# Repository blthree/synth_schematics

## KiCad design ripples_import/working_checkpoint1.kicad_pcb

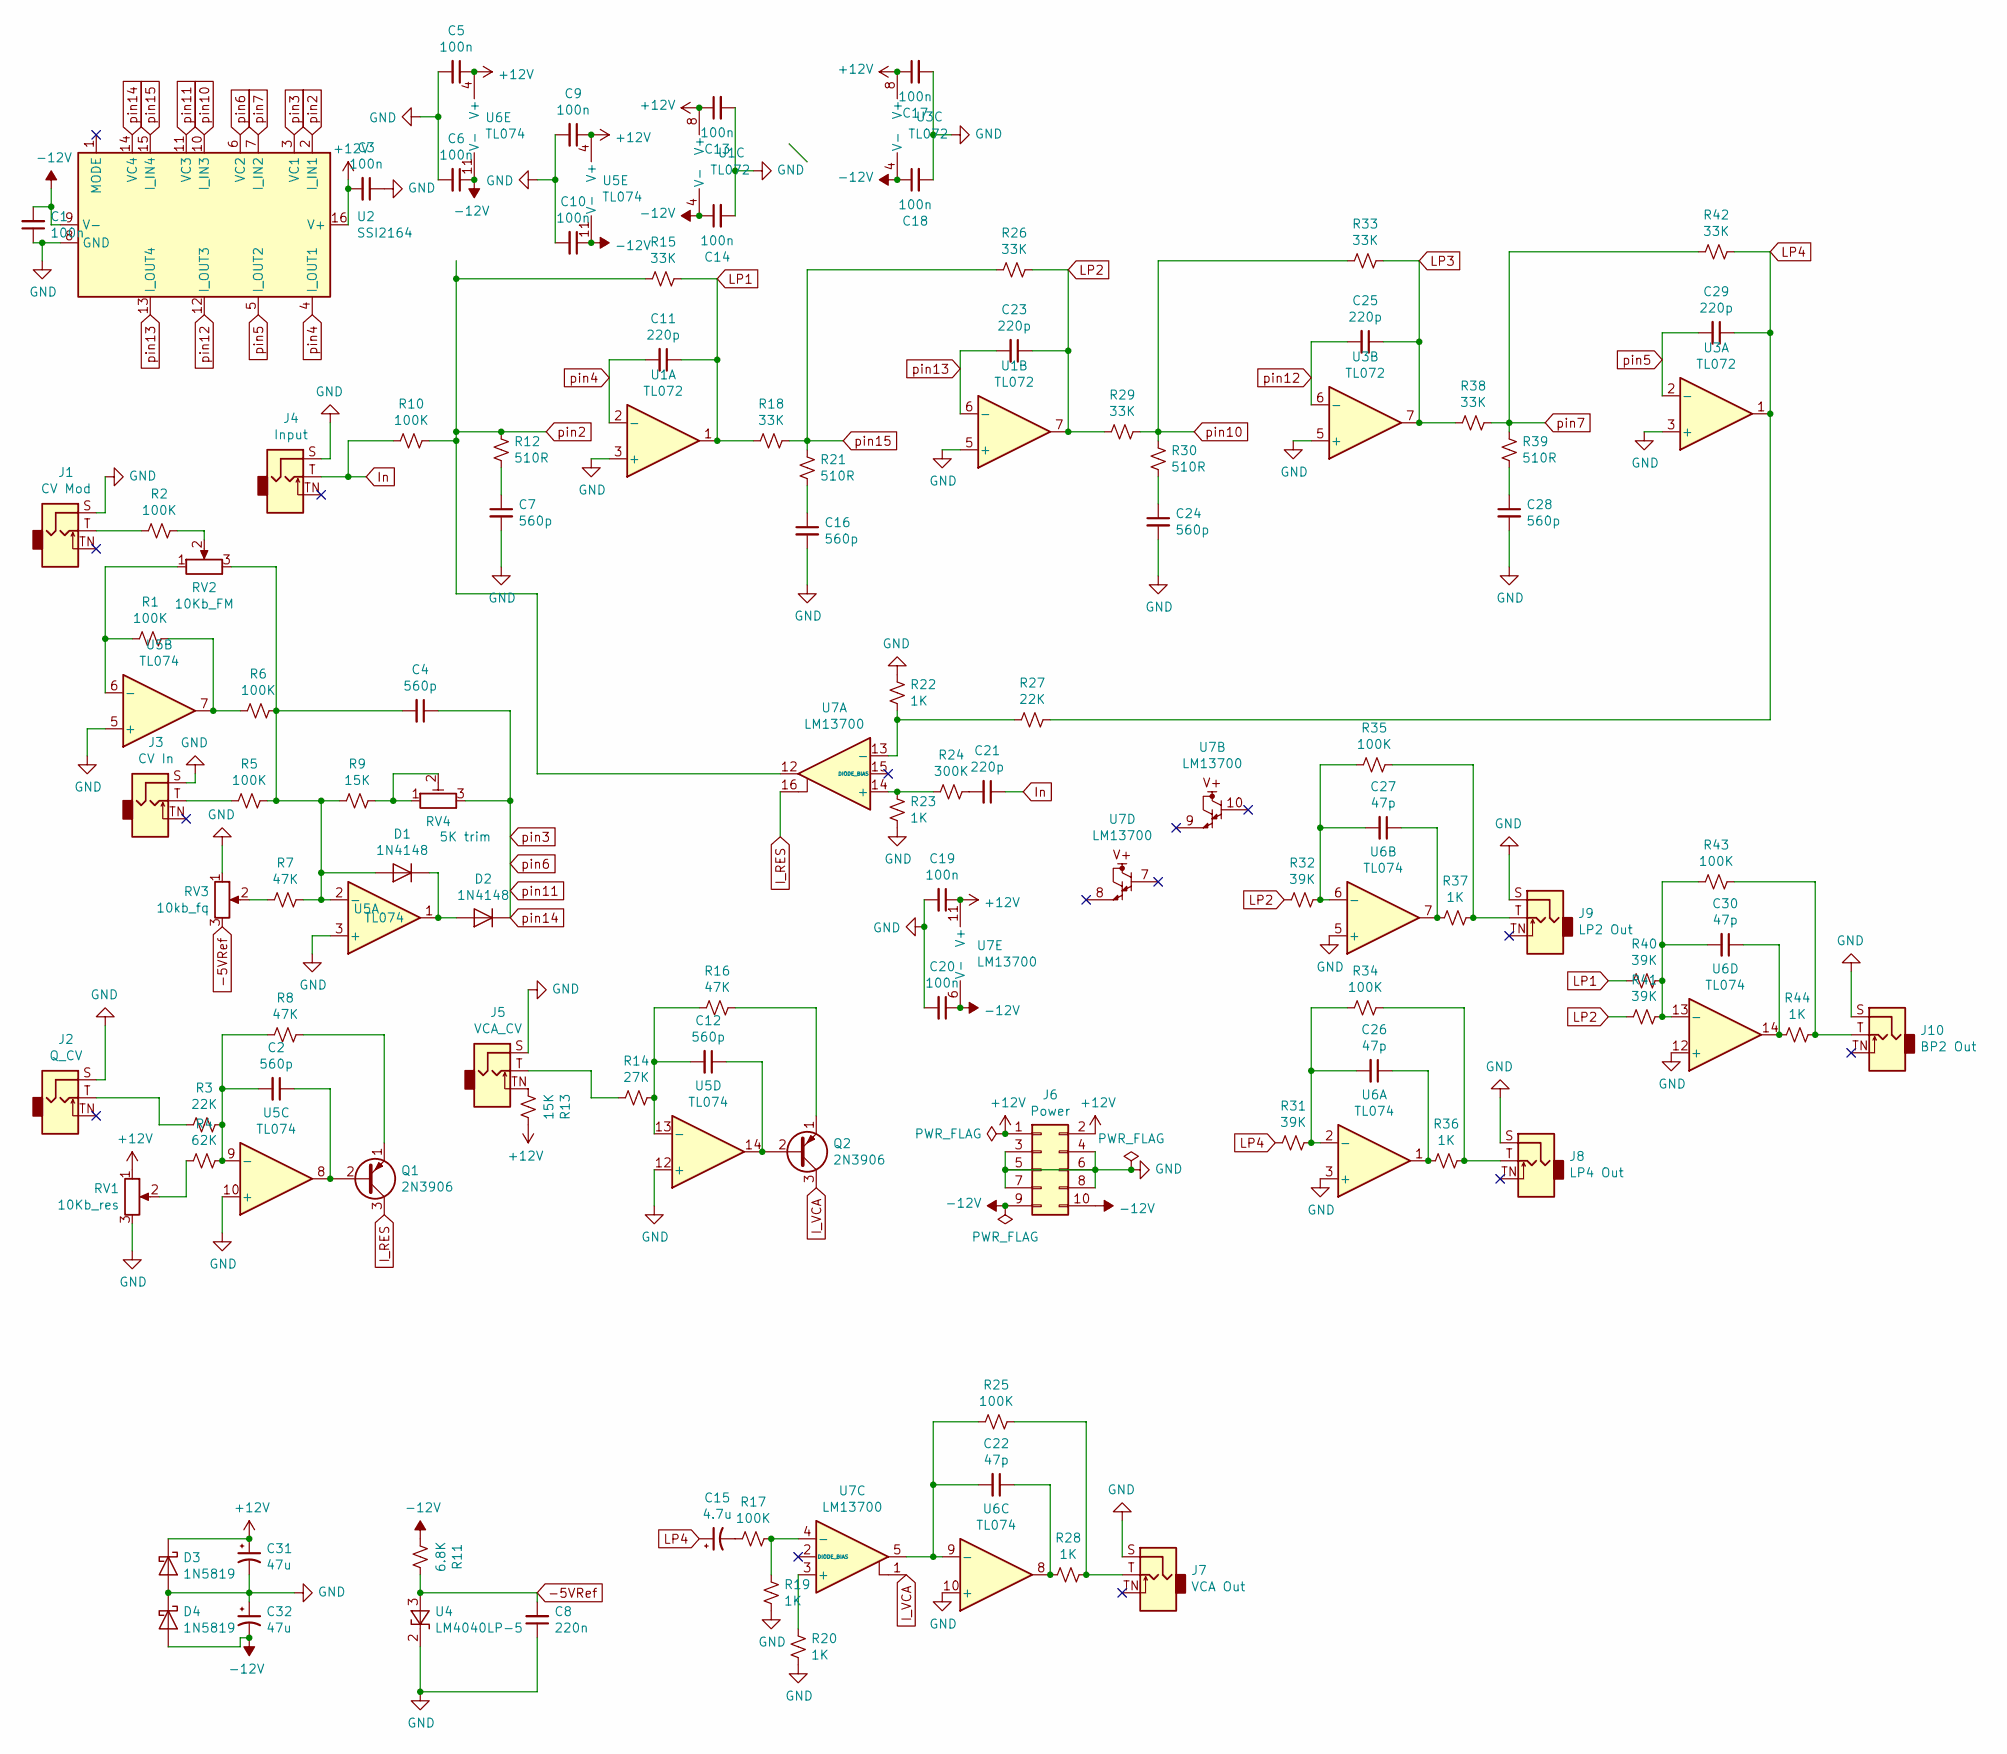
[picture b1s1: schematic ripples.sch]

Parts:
C1, C3, C5, C6, C9, C10, C13, C14, C17, C18, C19, C20: 100n; C_Disc_D5.1mm_W3.2mm_P5.00mm
C2, C4, C7, C12, C16, C24, C28: 560p; C_Disc_D5.1mm_W3.2mm_P5.00mm
C8: 220n; C_Disc_D5.1mm_W3.2mm_P5.00mm
C11, C21, C23, C25, C29: 220p; C_Disc_D5.1mm_W3.2mm_P5.00mm
C15: 4.7u; CP_Radial_D5.0mm_P2.00mm
C22, C26, C27, C30: 47p; C_Disc_D5.1mm_W3.2mm_P5.00mm
C31, C32: 47u; CP_Radial_D5.0mm_P2.00mm
D1, D2: 1N4148; D_DO-35_SOD27_P7.62mm_Horizontal
D3, D4: 1N5819; D_DO-41_SOD81_P10.16mm_Horizontal
J1: CV Mod; Jack_3.5mm_QingPu_WQP-PJ398SM_Vertical_CircularHoles
J2: Q_CV; Jack_3.5mm_QingPu_WQP-PJ398SM_Vertical_CircularHoles
J3: CV In; Jack_3.5mm_QingPu_WQP-PJ398SM_Vertical_CircularHoles
J4: Input; Jack_3.5mm_QingPu_WQP-PJ398SM_Vertical_CircularHoles
J5: VCA_CV; Jack_3.5mm_QingPu_WQP-PJ398SM_Vertical_CircularHoles
J6: Power; PinHeader_2x05_P2.54mm_Vertical
J7: VCA Out; Jack_3.5mm_QingPu_WQP-PJ398SM_Vertical_CircularHoles
J8: LP4 Out; Jack_3.5mm_QingPu_WQP-PJ398SM_Vertical_CircularHoles
J9: LP2 Out; Jack_3.5mm_QingPu_WQP-PJ398SM_Vertical_CircularHoles
J10: BP2 Out; Jack_3.5mm_QingPu_WQP-PJ398SM_Vertical_CircularHoles
Q1, Q2: 2N3906; TO-92_Inline
R1, R2, R5, R6, R10, R17, R25, R34, R35, R43: 100K; R_Axial_DIN0207_L6.3mm_D2.5mm_P5.08mm_Vertical
R3, R27: 22K; R_Axial_DIN0207_L6.3mm_D2.5mm_P5.08mm_Vertical
R4: 62K; R_Axial_DIN0207_L6.3mm_D2.5mm_P5.08mm_Vertical
R7, R8, R16: 47K; R_Axial_DIN0207_L6.3mm_D2.5mm_P5.08mm_Vertical
R9, R13: 15K; R_Axial_DIN0207_L6.3mm_D2.5mm_P5.08mm_Vertical
R11: 6.8K; R_Axial_DIN0207_L6.3mm_D2.5mm_P5.08mm_Vertical
R12, R21, R30, R39: 510R; R_Axial_DIN0207_L6.3mm_D2.5mm_P5.08mm_Vertical
R14: 27K; R_Axial_DIN0207_L6.3mm_D2.5mm_P5.08mm_Vertical
R15, R18, R26, R29, R33, R38, R42: 33K; R_Axial_DIN0207_L6.3mm_D2.5mm_P5.08mm_Vertical
R19, R20, R22, R23, R28, R36, R37, R44: 1K; R_Axial_DIN0207_L6.3mm_D2.5mm_P5.08mm_Vertical
R24: 300K; R_Axial_DIN0207_L6.3mm_D2.5mm_P5.08mm_Vertical
R31, R32, R40, R41: 39K; R_Axial_DIN0207_L6.3mm_D2.5mm_P5.08mm_Vertical
RV1: 10Kb_res; Potentiometer_Bourns_PTV09A-1_Single_Vertical
RV2: 10Kb_FM; Potentiometer_Bourns_PTV09A-1_Single_Vertical
RV3: 10kb_fq; Potentiometer_Bourns_PTV09A-1_Single_Vertical
RV4: 5K trim; Potentiometer_Bourns_3296X_Horizontal
U1, U3: TL072; DIP-8_W7.62mm_Socket
U2: SSI2164; DIP-16_W7.62mm_Socket
U4: LM4040LP-5; TO-92_Inline
U5, U6: TL074; DIP-14_W7.62mm_Socket
U7: LM13700; DIP-16_W7.62mm_Socket

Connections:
+12V: C3.2, C5.1, C9.1, C13.1, C17.1, C19.1, C31.1, D3.1 (K), J6.1, J6.2, R13.1, RV1.1, U1.8 (V+), U2.16 (V+), U3.8 (V+), U5.4 (V+), U6.4 (V+), U7.11 (V+)
-5VRef: C8.2, R11.1, RV3.3, U4.3 (A)
-12V: C1.2, C6.1, C10.1, C14.1, C18.1, C20.1, C32.2, D4.2 (A), J6.9, J6.10, R11.2, U1.4 (V-), U2.9 (V-), U3.4 (V-), U5.11 (V-), U6.11 (V-), U7.6 (V-)
GND: C1.1, C3.1, C5.2, C6.2, C7.2, C8.1, C9.2, C10.2, C13.2, C14.2, C16.2, C17.2, C18.2, C19.2, C20.2, C24.2, C28.2, C31.2, C32.1, D3.2 (A), D4.1 (K), J1.S, J2.S, J3.S, J4.S, J5.S, J6.3, J6.4, J6.5, J6.6, J6.7, J6.8, J7.S, J8.S, J9.S, J10.S, R19.1, R20.1, R22.2, R23.1, RV1.3, RV3.1, U1.3 (+), U1.5 (+), U2.8 (GND), U3.3 (+), U3.5 (+), U4.2 (K), U5.3 (+), U5.5 (+), U5.10 (+), U5.12 (+), U6.3 (+), U6.5 (+), U6.10 (+), U6.12 (+)
I_RES: Q1.3 (C), U7.16
I_VCA: Q2.3 (C), U7.1
In: C21.1, J4.T, R10.2
LP1: C11.1, R15.2, R18.1, R40.2, U1.1
LP2: C23.1, R26.2, R29.1, R32.2, R41.2, U1.7
LP3: C25.1, R33.2, R38.1, U3.7
LP4: C15.1, C29.1, R27.2, R31.2, R42.2, U3.1
unnamed: C2.1, Q1.2 (B), U5.8
unnamed: C2.2, R3.1, R4.1, R8.2, U5.9 (-)
unnamed: C4.2, D1.2 (A), R5.1, R6.1, R7.1, R9.2, RV2.3, U5.2 (-)
unnamed: C7.1, R12.1
unnamed: C12.1, Q2.2 (B), U5.14
unnamed: C12.2, R14.1, R16.2, U5.13 (-)
unnamed: C15.2, R17.2
unnamed: C16.1, R21.1
unnamed: C21.2, R24.2
unnamed: C22.1, R28.1, U6.8
unnamed: C22.2, R25.2, U6.9 (-), U7.5
unnamed: C24.1, R30.1
unnamed: C26.1, R36.1, U6.1
unnamed: C26.2, R31.1, R34.2, U6.2 (-)
unnamed: C27.1, R37.1, U6.7
unnamed: C27.2, R32.1, R35.2, U6.6 (-)
unnamed: C28.1, R39.1
unnamed: C30.1, R44.1, U6.14
unnamed: C30.2, R40.1, R41.1, R43.2, U6.13 (-)
unnamed: D1.1 (K), D2.2 (A), U5.1
unnamed: J1.T, R2.2
unnamed: J2.T, R3.2
unnamed: J3.T, R5.2
unnamed: J5.T, R14.2
unnamed: J5.TN, R13.2
unnamed: J7.T, R25.1, R28.2
unnamed: J8.T, R34.1, R36.2
unnamed: J9.T, R35.1, R37.2
unnamed: J10.T, R43.1, R44.2
unnamed: Q1.1 (E), R8.1
unnamed: Q2.1 (E), R16.1
unnamed: R1.1, R6.2, U5.7
unnamed: R1.2, RV2.1, U5.6 (-)
unnamed: R2.1, RV2.2
unnamed: R4.2, RV1.2
unnamed: R7.2, RV3.2
unnamed: R9.1, RV4.1, RV4.2
unnamed: R17.1, R19.2, U7.4 (-)
unnamed: R20.2, U7.3 (+)
unnamed: R22.1, R27.1, U7.13 (-)
unnamed: R23.2, R24.1, U7.14 (+)
pin2: R10.1, R12.2, R15.1, U2.2 (I_IN1), U7.12
pin4: C11.2, U1.2 (-), U2.4 (I_OUT1)
pin5: C29.2, U2.5 (I_OUT2), U3.2 (-)
pin7: R38.2, R39.2, R42.1, U2.7 (I_IN2)
pin10: R29.2, R30.2, R33.1, U2.10 (I_IN3)
pin11: C4.1, D2.1 (K), RV4.3, U2.3 (VC1), U2.6 (VC2), U2.11 (VC3), U2.14 (VC4)
pin12: C25.2, U2.12 (I_OUT3), U3.6 (-)
pin13: C23.2, U1.6 (-), U2.13 (I_OUT4)
pin15: R18.2, R21.2, R26.1, U2.15 (I_IN4)

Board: 2 copper layers, 103 parts (0 on the bottom side), 61 nets, no tracks yet.

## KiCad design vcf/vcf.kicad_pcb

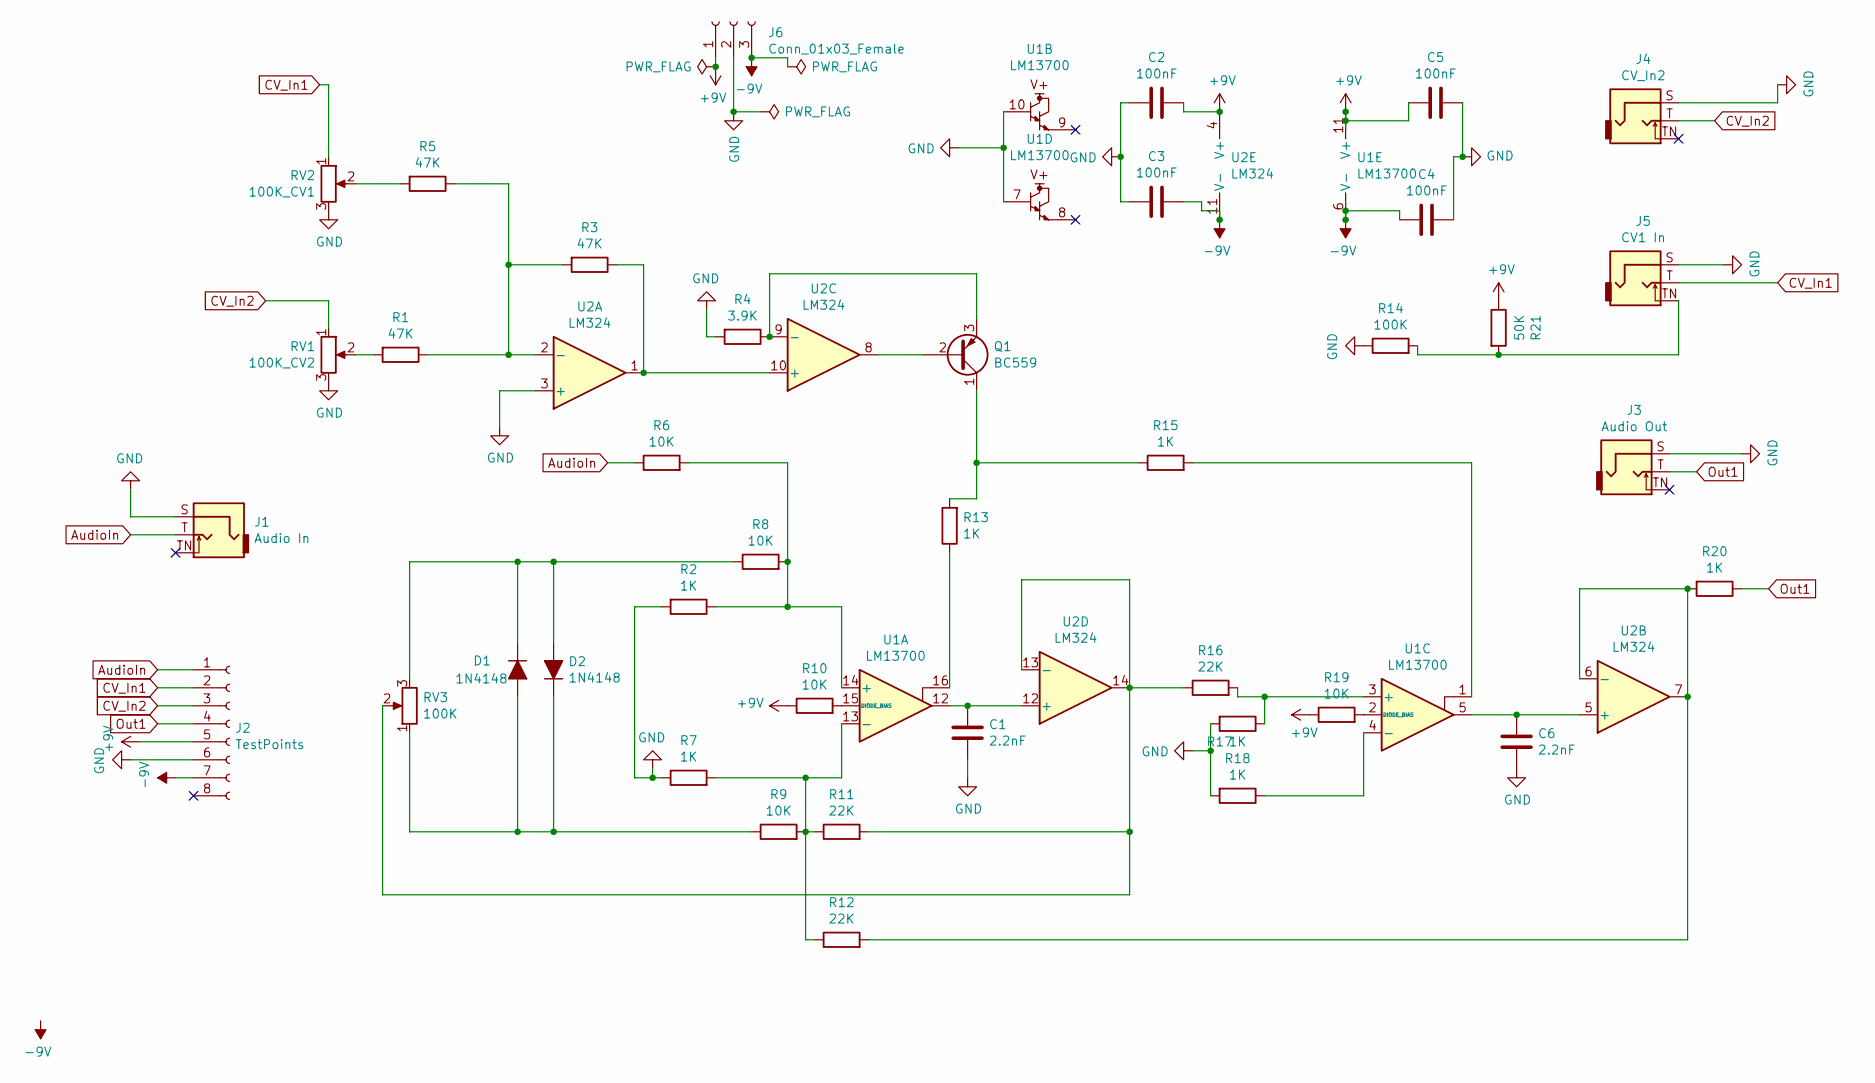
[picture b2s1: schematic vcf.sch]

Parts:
C1, C6: 2.2nF; C_Disc_D5.0mm_W2.5mm_P5.00mm
C2, C3, C4, C5: 100nF; C_Disc_D5.0mm_W2.5mm_P5.00mm
D1, D2: 1N4148; D_DO-35_SOD27_P7.62mm_Horizontal
J1: Audio In; CUI_SJ2-3592B-SMT-TR
J2: TestPoints; PinHeader_1x08_P2.54mm_Vertical
J3: Audio Out; CUI_SJ2-3592B-SMT-TR
J4: CV_In2; CUI_SJ2-3592B-SMT-TR
J5: CV1 In; CUI_SJ2-3592B-SMT-TR
J6: Conn_01x03_Female; JST_PH_B3B-PH-K_1x03_P2.00mm_Vertical
Q1: BC559; TO-92_Inline
R1, R3, R5: 47K; R_Axial_DIN0207_L6.3mm_D2.5mm_P5.08mm_Vertical
R2, R7, R13, R15, R17, R18, R20: 1K; R_Axial_DIN0207_L6.3mm_D2.5mm_P5.08mm_Vertical
R4: 3.9K; R_Axial_DIN0207_L6.3mm_D2.5mm_P5.08mm_Vertical
R6, R8, R9, R10, R19: 10K; R_Axial_DIN0207_L6.3mm_D2.5mm_P5.08mm_Vertical
R11, R12, R16: 22K; R_Axial_DIN0207_L6.3mm_D2.5mm_P5.08mm_Vertical
R14: 100K; R_Axial_DIN0207_L6.3mm_D2.5mm_P5.08mm_Vertical
R21: 50K; R_Axial_DIN0207_L6.3mm_D2.5mm_P5.08mm_Vertical
RV1: 100K_CV2; JST_PH_B3B-PH-K_1x03_P2.00mm_Vertical
RV2: 100K_CV1; JST_PH_B3B-PH-K_1x03_P2.00mm_Vertical
RV3: 100K; JST_PH_B3B-PH-K_1x03_P2.00mm_Vertical
U1: LM13700; DIP-16_W7.62mm_Socket
U2: LM324; DIP-14_W7.62mm_Socket

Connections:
+9V: C2.1, C5.2, J2.5, J6.1, R10.1, R19.1, R21.1, U1.11 (V+), U2.4 (V+)
-9V: C3.1, C4.2, J2.7, J6.3, U1.6 (V-), U2.11 (V-)
AudioIn: J1.T, J2.1, R6.1
CV_In1: J2.2, J5.T, RV2.1
CV_In2: J2.3, J4.T, RV1.1
GND: C1.2, C2.2, C3.2, C4.1, C5.1, C6.2, J1.S, J2.6, J3.S, J4.S, J5.S, J6.2, R2.2, R4.2, R7.1, R14.1, R17.2, R18.2, RV1.3, RV2.3, U1.7, U1.10, U2.3 (+)
unnamed: C1.1, U1.12, U2.12 (+)
unnamed: C6.1, U1.5, U2.5 (+)
unnamed: D1.1 (K), D2.2 (A), R8.1, RV3.3
unnamed: D1.2 (A), D2.1 (K), R9.1, RV3.1
unnamed: J5.TN, R14.2, R21.2
unnamed: Q1.1 (C), R13.2, R15.1
unnamed: Q1.2 (B), U2.8
unnamed: Q1.3 (E), R4.1, U2.9 (-)
unnamed: R1.1, R3.2, R5.1, U2.2 (-)
unnamed: R1.2, RV1.2
unnamed: R2.1, R6.2, R8.2, U1.14 (+)
unnamed: R3.1, U2.1, U2.10 (+)
unnamed: R5.2, RV2.2
unnamed: R10.2, U1.15 (DIODE_BIAS)
unnamed: R7.2, R9.2, R11.1, R12.1, U1.13 (-)
unnamed: R11.2, R16.1, RV3.2, U2.13 (-), U2.14
unnamed: R12.2, R20.2, U2.6 (-), U2.7
unnamed: R13.1, U1.16
unnamed: R15.2, U1.1
unnamed: R16.2, R17.1, U1.3 (+)
unnamed: R18.1, U1.4 (-)
unnamed: R19.2, U1.2 (DIODE_BIAS)
Out1: J2.4, J3.T, R20.1

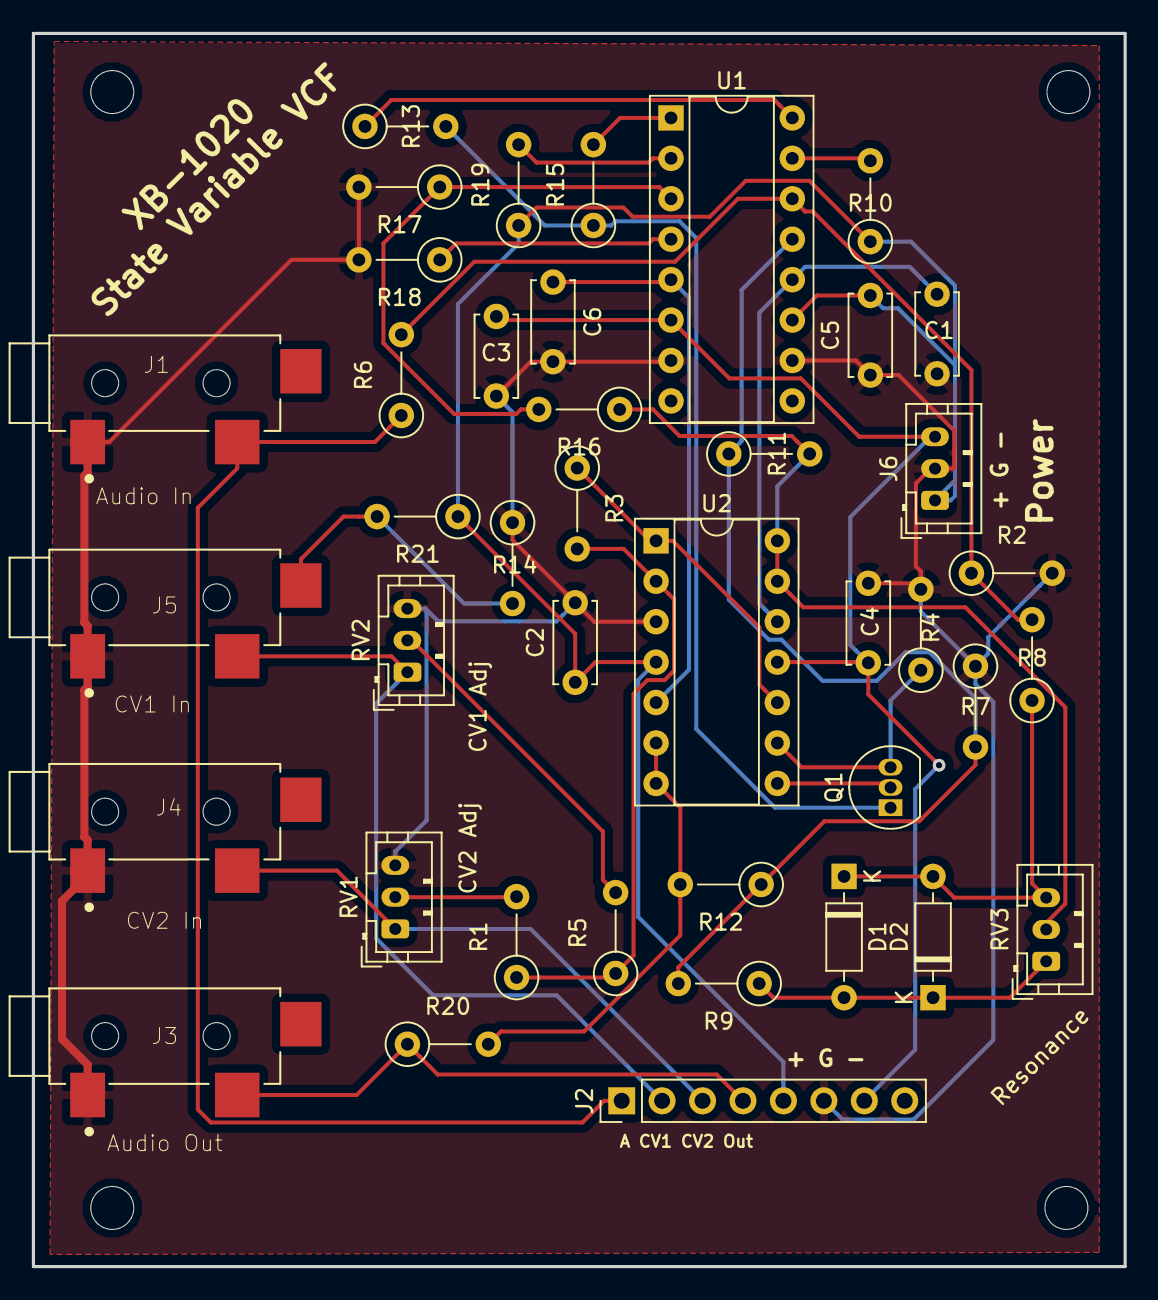
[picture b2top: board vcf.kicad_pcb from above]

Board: 2 copper layers, 68.6 x 77.5 mm, 41 parts (0 on the bottom side), 29 nets.

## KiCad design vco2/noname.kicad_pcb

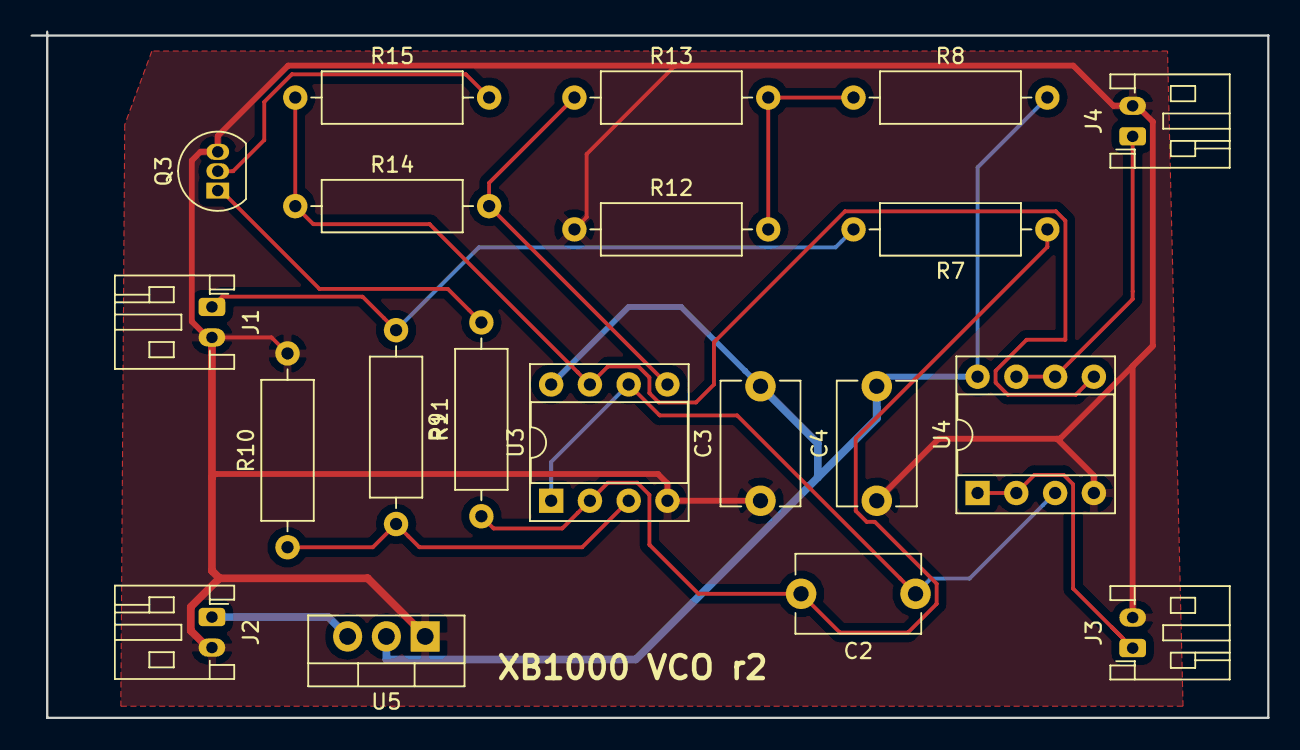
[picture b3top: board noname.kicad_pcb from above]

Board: 2 copper layers, 81.0 x 45.0 mm, 20 parts (0 on the bottom side), 14 nets.

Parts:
C2: 4.7nf; C_Disc_D8.0mm_W5.0mm_P7.50mm
C3, C4: 100nF; C_Disc_D8.0mm_W5.0mm_P7.50mm
J1: Input; JST_PH_S2B-PH-K_1x02_P2.00mm_Horizontal
J2: Power In; JST_PH_S2B-PH-K_1x02_P2.00mm_Horizontal
J3: Triangle Out; JST_PH_S2B-PH-K_1x02_P2.00mm_Horizontal
J4: Square Out; JST_PH_S2B-PH-K_1x02_P2.00mm_Horizontal
Q3: BC548; TO-92_Inline
R7, R8, R12, R14, R15: 100K; R_Axial_DIN0309_L9.0mm_D3.2mm_P12.70mm_Horizontal
R9, R10, R11, R13: 56K; R_Axial_DIN0309_L9.0mm_D3.2mm_P12.70mm_Horizontal
U3, U4: LM358; DIP-8_W7.62mm_Socket
U5: +5V Linear Regulator; TO-220-3_Vertical

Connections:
+5V: C3.2, C4.2, R8.2, U3.8, U4.8, U5.2
GND: C3.1, C4.1, J1.2, J2.2, J3.2, J4.2, Q3.3, R10.2, R12.1, U3.4, U4.4, U5.1
unnamed: C2.1, U3.1, U3.6, U4.3
unnamed: C2.2, R7.1, R11.1, U3.2
unnamed: J1.1, R7.2, R9.1
unnamed: J2.1, U5.3
unnamed: J3.1, U4.1, U4.2
unnamed: J4.1, U4.6, U4.7
unnamed: Q3.1, R11.2
unnamed: Q3.2, R15.2
unnamed: R9.2, R10.1, U3.3
unnamed: R8.1, R12.2, R13.2
unnamed: R13.1, R14.2, U3.5
unnamed: R14.1, R15.1, U3.7, U4.5

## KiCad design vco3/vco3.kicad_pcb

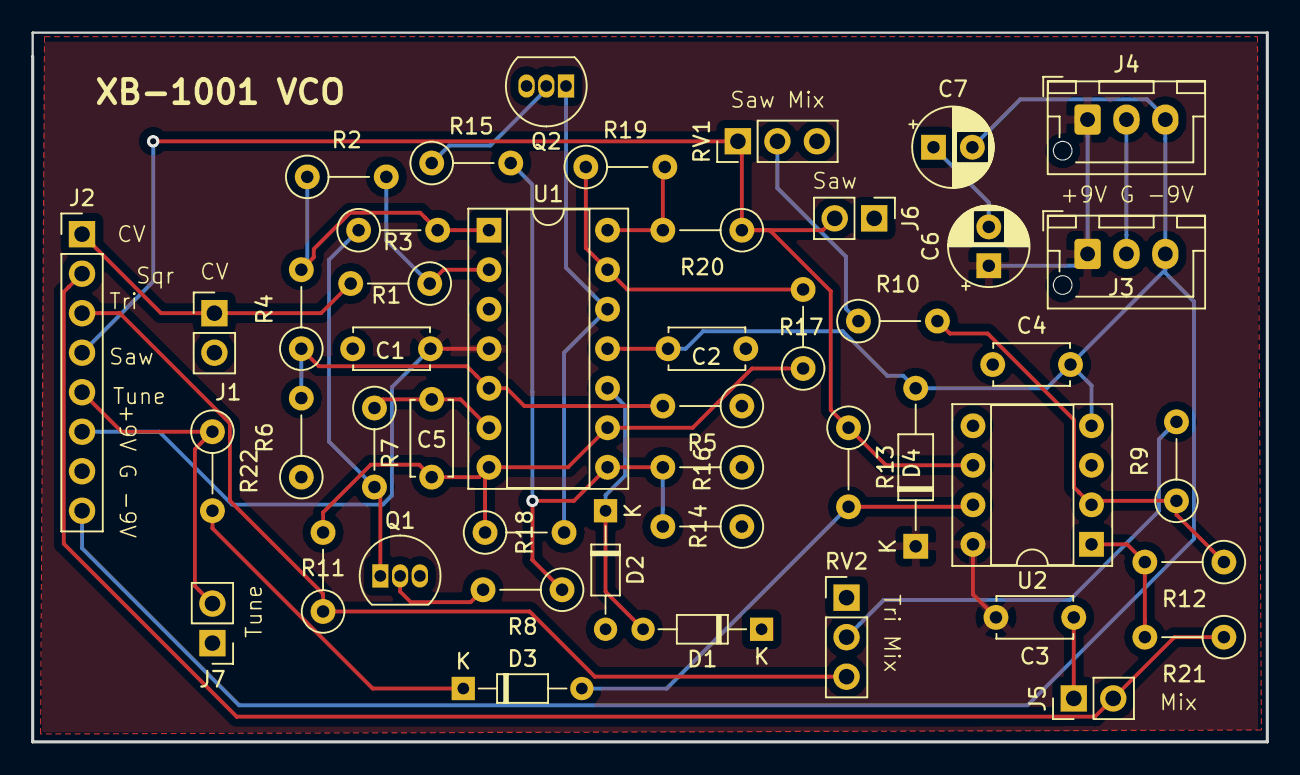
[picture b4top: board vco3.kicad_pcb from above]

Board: 2 copper layers, 79.4 x 45.6 mm, 46 parts (0 on the bottom side), 27 nets.

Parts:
C1, C2, C3, C4: 100nF; C_Disc_D4.7mm_W2.5mm_P5.00mm
C5: 47nF; C_Disc_D4.7mm_W2.5mm_P5.00mm
C6, C7: CP; CP_Radial_D5.0mm_P2.50mm
D1, D2, D3: 1N4148; D_DO-34_SOD68_P7.62mm_Horizontal
D4: 1N4001; D_DO-35_SOD27_P10.16mm_Horizontal
J1: CV Input; PinHeader_1x02_P2.54mm_Vertical
J2: Test Points; PinHeader_1x08_P2.54mm_Vertical
J3: Power A; JST_XH_B03B-XH-AM_1x03_P2.50mm_Vertical
J4: Power B; JST_XH_B03B-XH-AM_1x03_P2.50mm_Vertical
J5: Mix Out; PinHeader_1x02_P2.54mm_Vertical
J6: Saw Out; PinHeader_1x02_P2.54mm_Vertical
J7: Tune Out; PinHeader_1x02_P2.54mm_Vertical
Q1: BC559; TO-92_Inline
Q2: BC549; TO-92_Inline
R1, R2: 47K; R_Axial_DIN0207_L6.3mm_D2.5mm_P5.08mm_Vertical
R3, R7, R8, R15: 22K; R_Axial_DIN0207_L6.3mm_D2.5mm_P5.08mm_Vertical
R4, R5, R6, R13, R14, R17, R18, R19: 100K; R_Axial_DIN0207_L6.3mm_D2.5mm_P5.08mm_Vertical
R9, R10: 10K; R_Axial_DIN0207_L6.3mm_D2.5mm_P5.08mm_Vertical
R11, R16, R20, R21, R22: 1K; R_Axial_DIN0207_L6.3mm_D2.5mm_P5.08mm_Vertical
R12: 56K; R_Axial_DIN0207_L6.3mm_D2.5mm_P5.08mm_Vertical
RV1, RV2: 100K; PinHeader_1x03_P2.54mm_Vertical
U1: LM324; DIP-14_W7.62mm_Socket
U2: TL072; DIP-8_W7.62mm_Socket

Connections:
+9V: C1.2, C3.2, C6.1, D4.1, J2.6, J3.1, J4.1, U1.4, U2.8
-9V: C2.2, C4.2, C7.2, D4.2, J2.8, J3.3, J4.3, U1.11, U2.4
CV_In: J1.1, J2.1, R1.2
GND: C1.1, C2.1, C3.1, C4.1, C6.2, C7.1, D1.1, D2.2, J1.2, J2.7, J3.2, J4.2, J5.1, J6.1, J7.1, Q1.3, Q2.3, R5.1, R6.1, R14.1, U1.3, U2.3, U2.5
MixOut: J2.2, J5.2, R21.1
unnamed: C5.1, R11.2, R17.1, R18.1, U1.7, U1.9
unnamed: C5.2, R7.1, U1.6
unnamed: D1.2, D2.1, U1.10
unnamed: D3.1, R22.2
unnamed: D3.2, R13.2, U2.7
unnamed: Q1.1, R3.1, R7.2
unnamed: Q1.2, R8.2
unnamed: Q2.1, R18.2, U1.12
unnamed: Q2.2, R15.1
unnamed: R1.1, R2.2, U1.2
unnamed: R2.1, R3.2, R4.2, U1.1
unnamed: R4.1, R5.2, R6.2, U1.5
unnamed: R9.2, RV2.2
unnamed: R10.1, RV1.2
unnamed: R9.1, R10.2, R12.1, U2.2
unnamed: R12.2, R21.2, U2.1
unnamed: R8.1, R14.2, R15.2, R16.2, U1.8
unnamed: R17.2, R19.1, U1.13
unnamed: R19.2, R20.2, U1.14
SawOut: J2.4, J6.2, R13.1, R20.1, RV1.1, U2.6
SubTriOut: J2.3, R11.1, RV2.3
TuneOut: J2.5, J7.2, R22.1

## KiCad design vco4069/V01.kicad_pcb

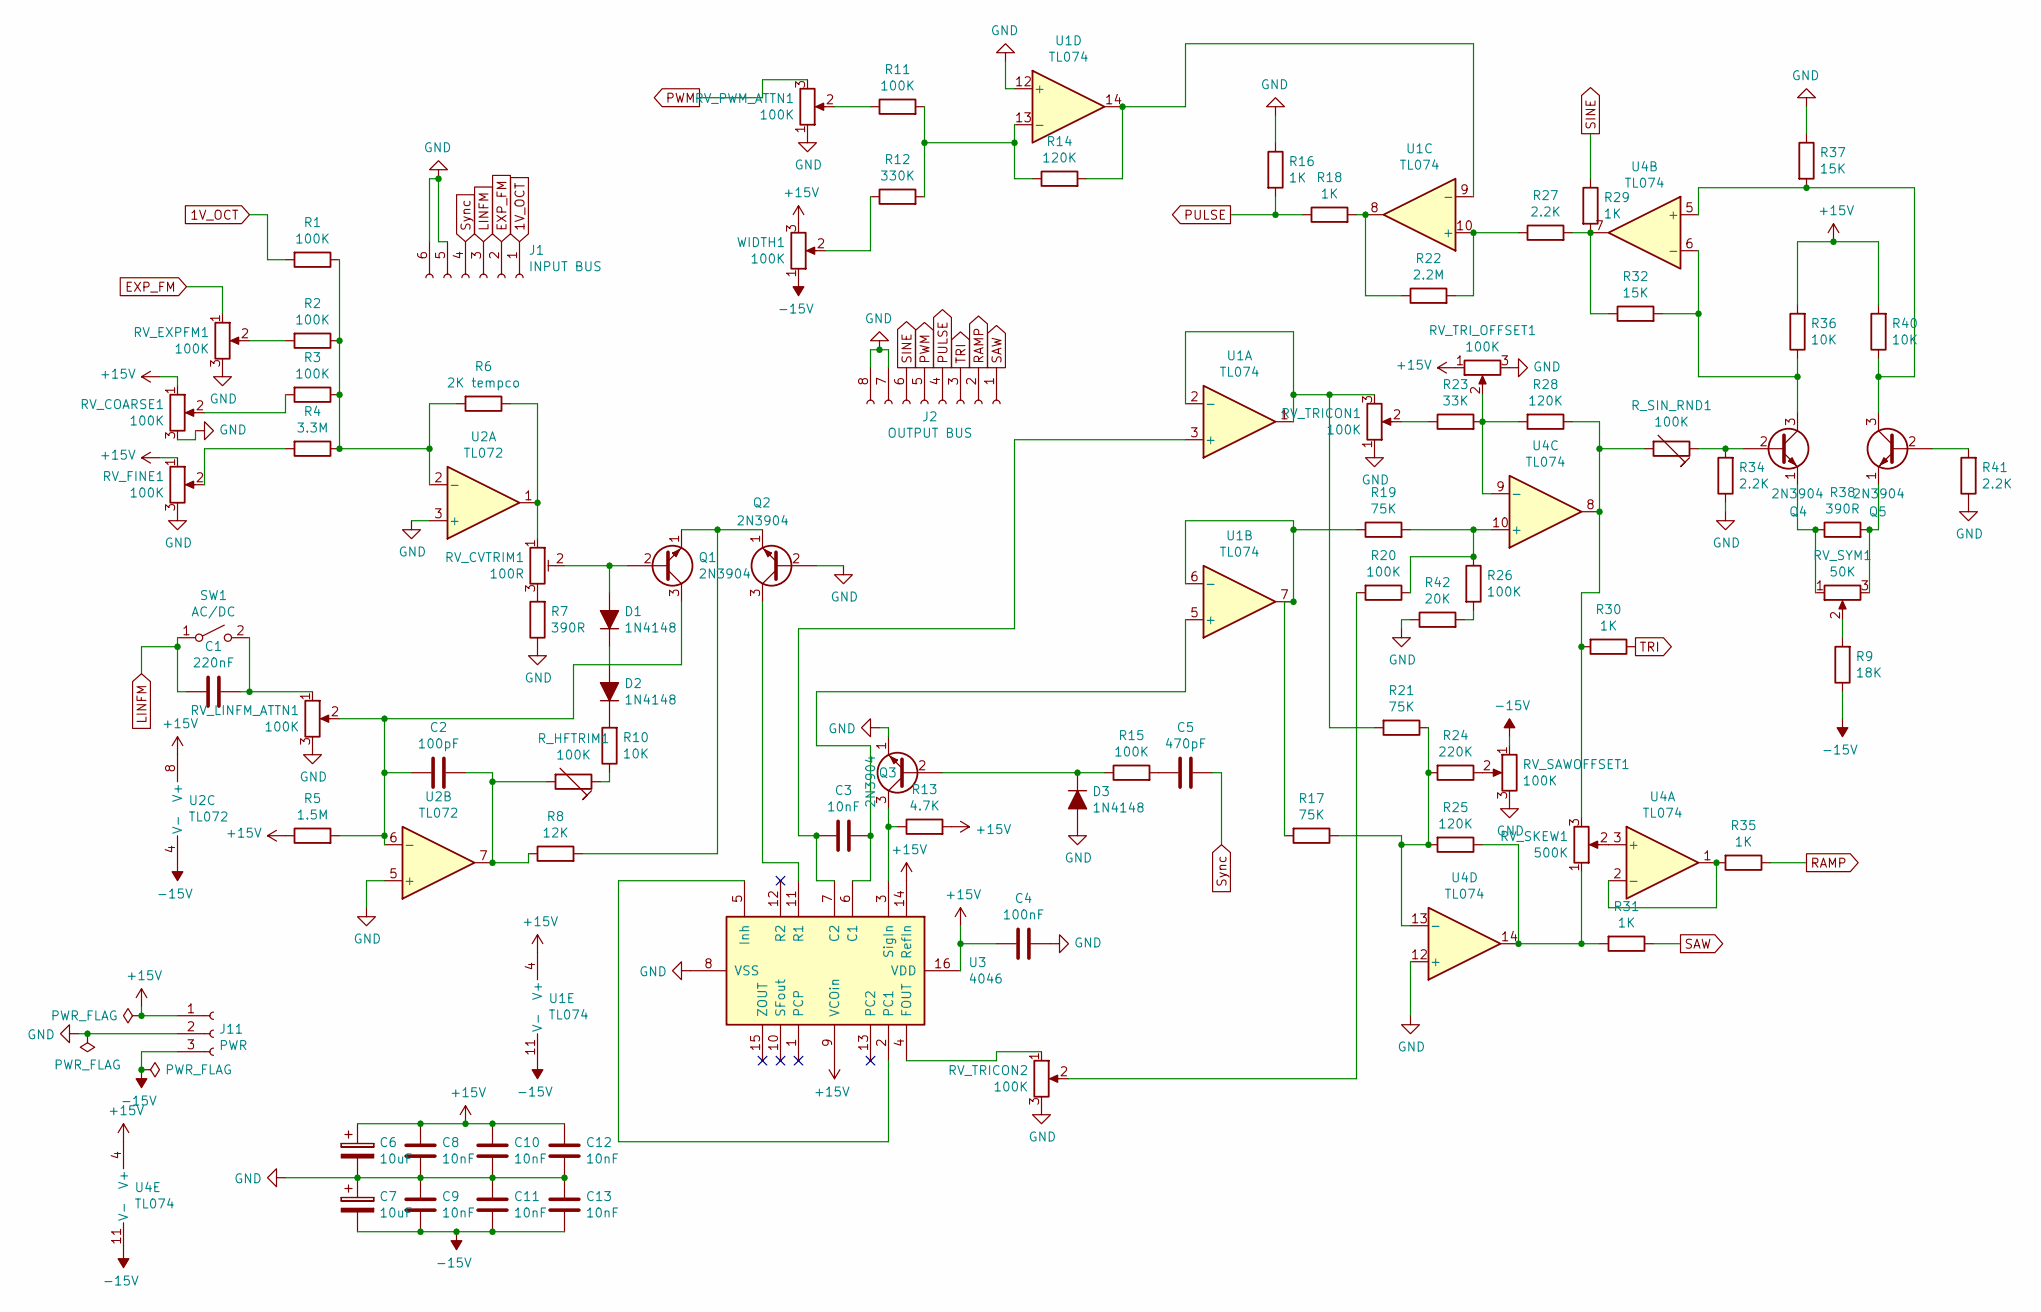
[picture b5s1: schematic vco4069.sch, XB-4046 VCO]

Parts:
C1: 220nF; C_Disc_D4.7mm_W2.5mm_P5.00mm
C2: 100pF; C_Disc_D4.7mm_W2.5mm_P5.00mm
C3, C8, C9, C10, C11, C12, C13: 10nF; C_Disc_D4.7mm_W2.5mm_P5.00mm
C4: 100nF; C_Disc_D4.7mm_W2.5mm_P5.00mm
C5: 470pF; C_Disc_D4.7mm_W2.5mm_P5.00mm
C6, C7: 10uF; CP_Radial_D10.0mm_P5.00mm
D1, D2, D3: 1N4148; D_DO-35_SOD27_P7.62mm_Horizontal
J1: INPUT BUS; PinHeader_1x06_P2.54mm_Vertical
J2: OUTPUT BUS; PinHeader_1x08_P2.54mm_Vertical
J11: PWR; PinHeader_1x03_P2.54mm_Vertical
Q1, Q2, Q3, Q4, Q5: 2N3904; TO-92_Inline
R1, R2, R3, R11, R15, R20, R26: 100K; R_Axial_DIN0207_L6.3mm_D2.5mm_P5.08mm_Vertical
R4: 3.3M; R_Axial_DIN0207_L6.3mm_D2.5mm_P5.08mm_Vertical
R5: 1.5M; R_Axial_DIN0207_L6.3mm_D2.5mm_P5.08mm_Vertical
R6: 2K tempco; R_Axial_DIN0207_L6.3mm_D2.5mm_P5.08mm_Vertical
R7, R38: 390R; R_Axial_DIN0207_L6.3mm_D2.5mm_P5.08mm_Vertical
R8: 12K; R_Axial_DIN0207_L6.3mm_D2.5mm_P5.08mm_Vertical
R9: 18K; R_Axial_DIN0207_L6.3mm_D2.5mm_P5.08mm_Vertical
R10, R36, R40: 10K; R_Axial_DIN0207_L6.3mm_D2.5mm_P5.08mm_Vertical
R12: 330K; R_Axial_DIN0207_L6.3mm_D2.5mm_P5.08mm_Vertical
R13: 4.7K; R_Axial_DIN0207_L6.3mm_D2.5mm_P5.08mm_Vertical
R14, R25, R28: 120K; R_Axial_DIN0207_L6.3mm_D2.5mm_P5.08mm_Vertical
R16, R18, R29, R30, R31, R35: 1K; R_Axial_DIN0207_L6.3mm_D2.5mm_P5.08mm_Vertical
R17, R19, R21: 75K; R_Axial_DIN0207_L6.3mm_D2.5mm_P5.08mm_Vertical
R22: 2.2M; R_Axial_DIN0207_L6.3mm_D2.5mm_P5.08mm_Vertical
R23: 33K; R_Axial_DIN0207_L6.3mm_D2.5mm_P5.08mm_Vertical
R24: 220K; R_Axial_DIN0207_L6.3mm_D2.5mm_P5.08mm_Vertical
R27, R34, R41: 2.2K; R_Axial_DIN0207_L6.3mm_D2.5mm_P5.08mm_Vertical
R32, R37: 15K; R_Axial_DIN0207_L6.3mm_D2.5mm_P5.08mm_Vertical
R42: 20K; R_Axial_DIN0207_L6.3mm_D2.5mm_P5.08mm_Vertical
RV_COARSE1: 100K; PinHeader_1x03_P2.54mm_Vertical
RV_CVTRIM1: 100R; Potentiometer_Bourns_3296Z_Horizontal
RV_EXPFM1: 100K; PinHeader_1x03_P2.54mm_Vertical
RV_FINE1: 100K; PinHeader_1x03_P2.54mm_Vertical
RV_LINFM_ATTN1: 100K; PinHeader_1x03_P2.54mm_Vertical
RV_PWM_ATTN1: 100K; PinHeader_1x03_P2.54mm_Vertical
RV_SAWOFFSET1: 100K; PinHeader_1x03_P2.54mm_Vertical
RV_SKEW1: 500K; PinHeader_1x03_P2.54mm_Vertical
RV_SYM1: 50K; Potentiometer_Bourns_3296W_Vertical
RV_TRICON1, RV_TRICON2: 100K; PinHeader_1x03_P2.54mm_Vertical
RV_TRI_OFFSET1: 100K; PinHeader_1x03_P2.54mm_Vertical
R_HFTRIM1: 100K; Potentiometer_Bourns_3296W_Vertical
R_SIN_RND1: 100K; Potentiometer_Bourns_3296W_Vertical
SW1: AC/DC; PinHeader_1x02_P2.54mm_Vertical
U1, U4: TL074; DIP-14_W7.62mm_Socket
U2: TL072; DIP-8_W7.62mm_Socket
U3: 4046; DIP-16_W7.62mm_Socket
WIDTH1: 100K; PinHeader_1x03_P2.54mm_Vertical

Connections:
1V_OCT: J1.1, R1.2
+15V: C4.2, C6.1, C8.2, C10.2, C12.2, J11.1, R5.1, R13.2, R36.2, R40.2, RV_COARSE1.1, RV_FINE1.1, RV_TRI_OFFSET1.1, U1.4 (V+), U2.8 (V+), U3.9 (VCOin), U3.14 (RefIn), U3.16 (VDD), U4.4 (V+), WIDTH1.3
-15V: C7.2, C9.1, C11.1, C13.1, J11.3, R9.1, RV_SAWOFFSET1.1, U1.11 (V-), U2.4 (V-), U4.11 (V-), WIDTH1.1
EXP_FM: J1.2, RV_EXPFM1.1
GND: C4.1, C6.2, C7.1, C8.1, C9.2, C10.1, C11.2, C12.1, C13.2, D3.2 (A), J1.5, J1.6, J2.7, J2.8, J11.2, Q2.2 (B), Q3.1 (E), R7.1, R16.1, R34.1, R37.1, R41.1, R42.1, RV_COARSE1.3, RV_EXPFM1.3, RV_FINE1.3, RV_LINFM_ATTN1.3, RV_PWM_ATTN1.1, RV_SAWOFFSET1.3, RV_TRICON1.1, RV_TRICON2.3, RV_TRI_OFFSET1.3, U1.12 (+), U2.3 (+), U2.5 (+), U3.8 (VSS), U4.12 (+)
LINFM: C1.2, J1.3, SW1.1 (A)
unnamed: C1.1, RV_LINFM_ATTN1.1, SW1.2 (B)
unnamed: C2.1, R8.1, R_HFTRIM1.2, U2.7
unnamed: C2.2, Q1.3 (C), R5.2, RV_LINFM_ATTN1.2, U2.6 (-)
unnamed: C3.1, U1.5 (+), U3.6 (C1)
unnamed: C3.2, U1.3 (+), U3.7 (C2)
unnamed: C5.2, R15.2
unnamed: D1.1 (K), D2.2 (A)
unnamed: D1.2 (A), Q1.2 (B), RV_CVTRIM1.2
unnamed: D2.1 (K), R10.2
unnamed: D3.1 (K), Q3.2 (B), R15.1
unnamed: Q1.1 (E), Q2.1 (E), R8.2
unnamed: Q2.3 (C), U3.11 (R1)
unnamed: Q3.3 (C), R13.1, U3.3 (SigIn)
unnamed: Q4.1 (E), R38.1, RV_SYM1.1
unnamed: Q4.2 (B), R34.2, R_SIN_RND1.1
unnamed: Q4.3 (C), R32.2, R36.1, U4.6 (-)
unnamed: Q5.1 (E), R38.2, RV_SYM1.3
unnamed: Q5.2 (B), R41.2
unnamed: Q5.3 (C), R37.2, R40.1, U4.5 (+)
unnamed: R1.1, R2.1, R3.1, R4.1, R6.2, U2.2 (-)
unnamed: R2.2, RV_EXPFM1.2
unnamed: R3.2, RV_COARSE1.2
unnamed: R4.2, RV_FINE1.2
unnamed: R6.1, RV_CVTRIM1.1, U2.1
unnamed: R7.2, RV_CVTRIM1.3
unnamed: R9.2, RV_SYM1.2
unnamed: R10.1, R_HFTRIM1.1
unnamed: R11.1, RV_PWM_ATTN1.2
unnamed: R11.2, R12.2, R14.1, U1.13 (-)
unnamed: R12.1, WIDTH1.2
unnamed: R14.2, U1.9 (-), U1.14
unnamed: R17.1, R21.1, R24.2, R25.2, U4.13 (-)
unnamed: R17.2, R19.1, U1.6 (-), U1.7
unnamed: R18.2, R22.1, U1.8
unnamed: R19.2, R20.1, R26.1, U4.10 (+)
unnamed: R20.2, RV_TRICON2.2
unnamed: R21.2, RV_TRICON1.3, U1.1, U1.2 (-)
unnamed: R22.2, R27.1, U1.10 (+)
unnamed: R23.1, RV_TRICON1.2
unnamed: R23.2, R28.2, RV_TRI_OFFSET1.2, U4.9 (-)
unnamed: R24.1, RV_SAWOFFSET1.2
unnamed: R25.1, R31.2, RV_SKEW1.1, U4.14
unnamed: R26.2, R42.2
unnamed: R27.2, R29.2, R32.1, U4.7
unnamed: R28.1, R30.2, RV_SKEW1.3, R_SIN_RND1.2, U4.8
unnamed: R35.2, U4.1, U4.2 (-)
unnamed: RV_SKEW1.2, U4.3 (+)
unnamed: RV_TRICON2.1, U3.4 (FOUT)
unnamed: U3.2 (PC1), U3.5 (Inh)
PULSE: J2.4, R16.2, R18.1
PWM: J2.5, RV_PWM_ATTN1.3
RAMP: J2.2, R35.1
SAW: J2.1, R31.1
SINE: J2.6, R29.1
Sync: C5.1, J1.4
TRI: J2.3, R30.1

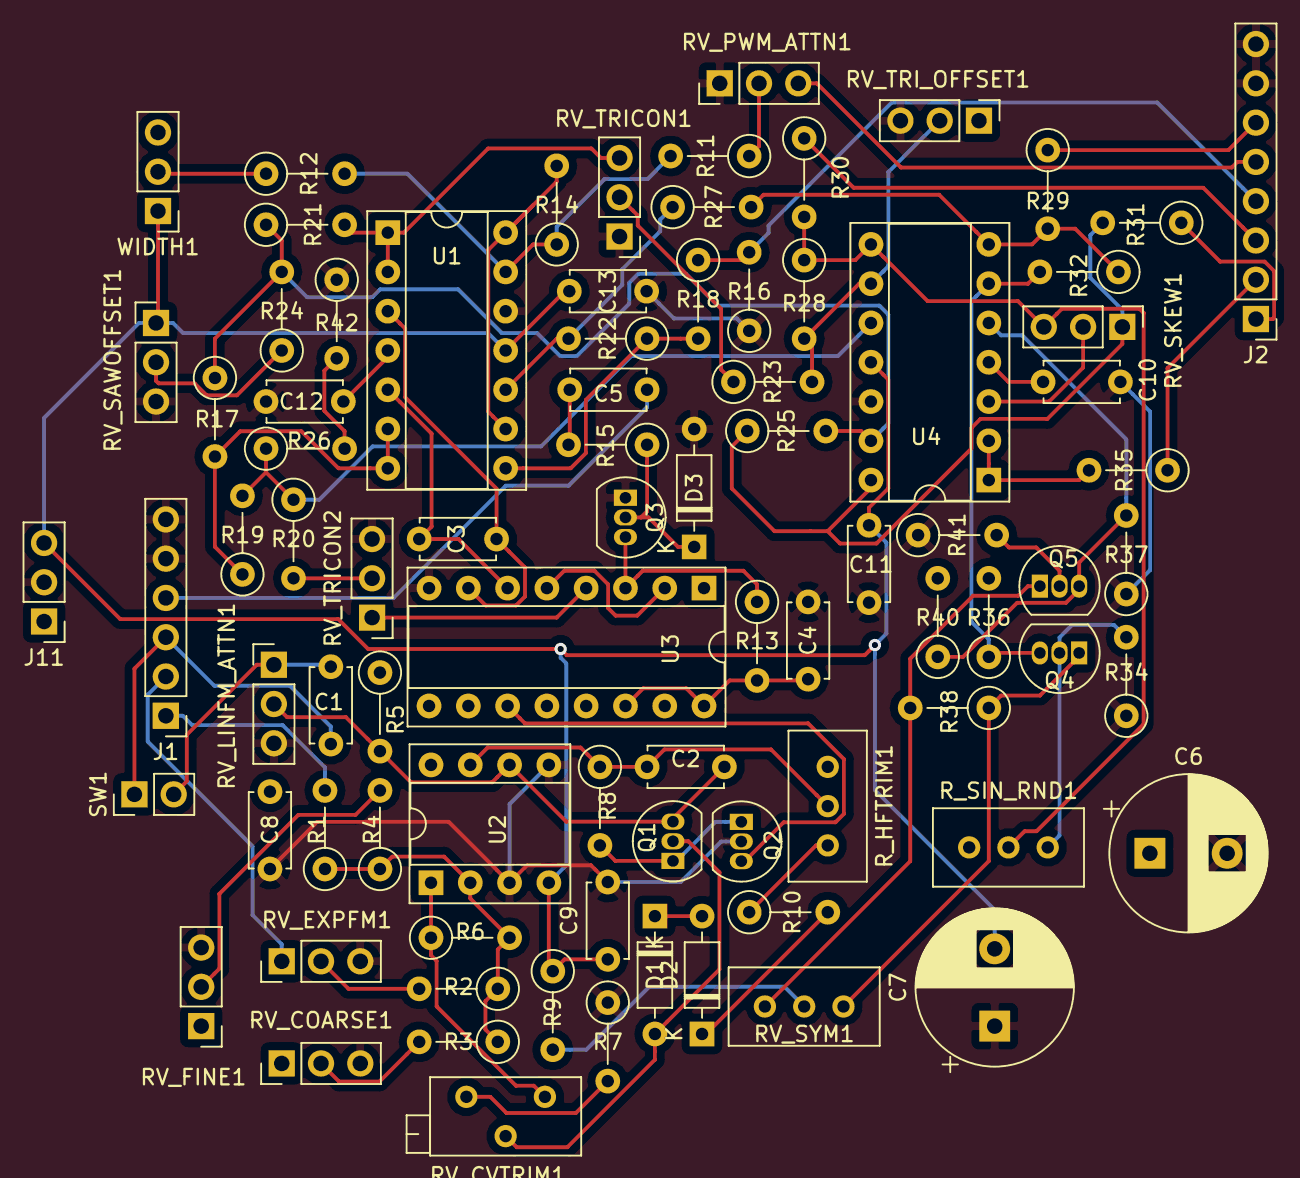
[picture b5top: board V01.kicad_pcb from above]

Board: 2 copper layers, 84 parts (0 on the bottom side), 62 nets.
